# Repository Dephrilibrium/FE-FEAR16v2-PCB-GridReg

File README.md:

# FEAR-Grid Regulation
This repository contains the KiCAD-design files for a shield of the F(ield) E(mission) A(rray) R(egulation) current control circuit.

**Note:** This project is part of the SubModule-repository [FE-FEAR16v2][FE-FEAR16v2-SubmoduleRepo], where you can find sub-repositories for other shield-PCBs, mainboard-PCB and the firmware.

# Description
The name "grid regulation" comes from the original main purpose of regulating the potential of the extraction grid (extraction voltage) of a field emission array (FEA = cathode) based on the current through the cathode. However, it can be used in all cases where a potential needs to be regulation (Grid-input) based on the current-flow through the device under test which can be connected on a separate measurement-input (FEA-input). During active regulation this shield acts like a current-source/-sink.

- The shield itself takes 1 DAC-output voltage (V~Ctrl~ = 0..10V) to adjust the current control.
- The A(mperemeter) is actually a shunt-resistor which defines the measurable current range. A 1MΩ for instance yields a range from 0.31 nA (resolution) to 10 µA, whereby its wisely to keep the current slightly below as 10 µA is the absolute maximum measurable value.
- The V(oltmeter) measures the internal voltage-drop over the FET.

**Note:** Both, A and V use potentiometers to adjust their feedback-loop amplification. Due to tolerances on all the parts, its recommended to use a shield only at a specific mainboard and a specific channel-position at which the boards were calibrated.

**Principle of the cathode regulation:**

# HowTo to connect (samples and for calibration)
1. Place a shield on a mainboard/channel-slot.

2. Calibration: continue with step 3., otherwise go to 5.

3. Calibrate V~Shnt~ (FEA-Input)

    1. Connect the positive supply of a voltage source (needs to supply voltages up to 10V) to the FEA-input via an amperemeter (see figure above) and the negative supply (GND) to the HV- input. Note that amperemeter for fine-tuning the V~Shnt~ measurement (FEA-Input) is located between FEA-Input and FEA for circuitry reasons. As over the GridReg-Shield a voltage-drop occurs (up to 10V), the amperemeter needs to be able to withstand a few volts between measurement input and earth.

    2. Apply a voltage to the input (e.g. 9V).

    3. Adjust the current gain potentiometer, so that the measured ADC value divided by the shunt-resistance is equal to the amperemeter-value (V~Shnt~/R~Shunt~ = I~Amperemeter~)

4. Calibrate V~Drp~ (Grid-Input)

    1. Make sure, the FEA-Input connection of 3.i. above was made.

    2. Connect a high voltage-supply (via a Load-Resistor R~L~) to the Grid-Supply-Input (for further explanations see note below) and apply a high voltage (e.g. 1kV).

    3. Adjust the FEA-input voltage of 3.ii., so that the NFET blocks the current flow (Grid-Potential should increase to 1kV). If the FEA-Input voltage has to be higher or lower than V~Ctrl~ depends if you use the additional inverter-option which can be connected to the NFET-gate on the PCB.

    4. Adjust the voltage-drop gain potentiometer. The board projects a voltage range of &pm;1500V into a range of &pm;10V using a voltage divider with huge resistance values. Example for positive voltage:
    1500V * 5GΩ / 1005GΩ * Gain = 7.462..V * Gain = 10V
    Gain = 10V / 7.462..V = 1.34

5. Connect your FEA on the shield's FEA-Input screw terminal, the extraction grid to the the most negative supply to to HV- (which is the mainboard's common-terminal).

**Note:**
- The load-resistor R~L~ is a simple approach of increasing the voltage on the Grid-Input. This is because the high voltage of up to 1500V makes a  performant half-bridge design (regulated PFET instead of R~L~) tricky to realize. Its also noteworthy that R~L~ creates an asymmetric time-behaviour in charging and discharging the voltage of the extraction grid, and depends on the speeds your applications require.
- The FEAR command-documentation can be found in the firmware-repository (see [FE-FEAR16v2 Submodule-Repo][FE-FEAR16v2-SubmoduleRepo]).

[FE-FEAR16v2-SubmoduleRepo]: https://github.com/Dephrilibrium/FE-FEAR16v2

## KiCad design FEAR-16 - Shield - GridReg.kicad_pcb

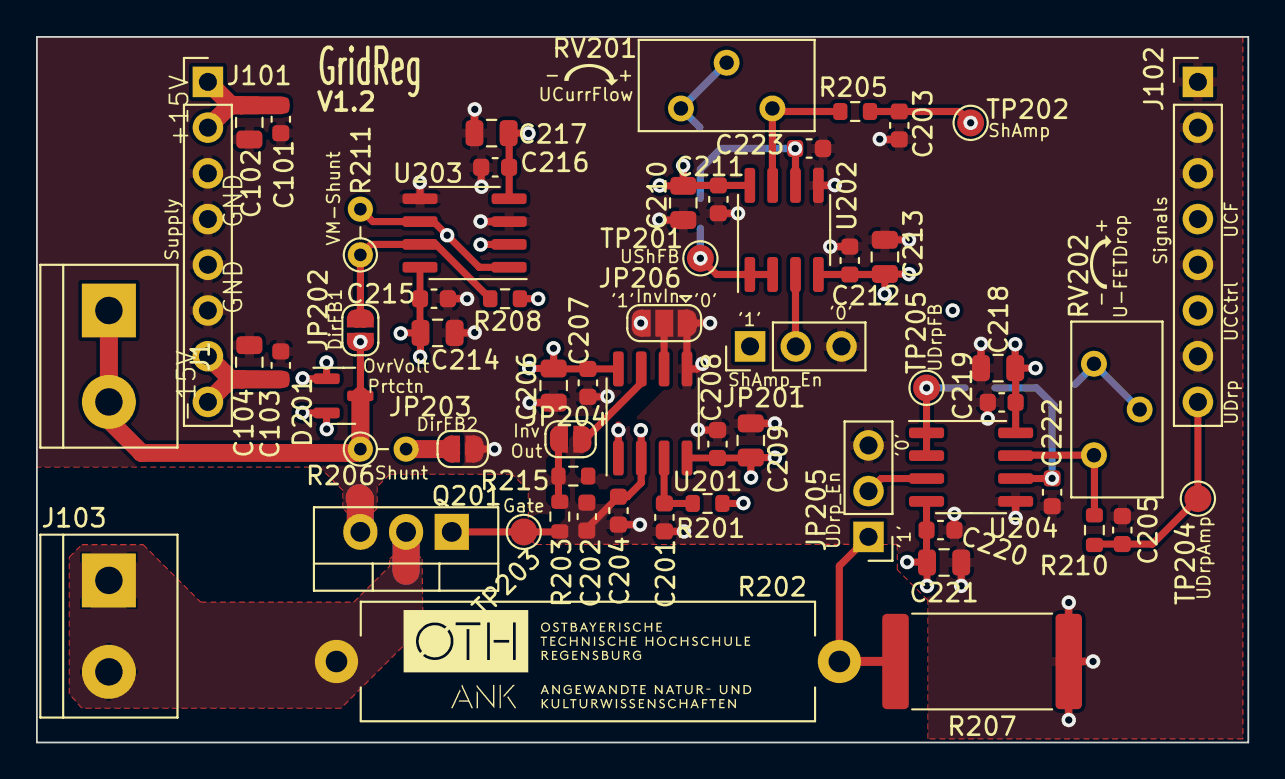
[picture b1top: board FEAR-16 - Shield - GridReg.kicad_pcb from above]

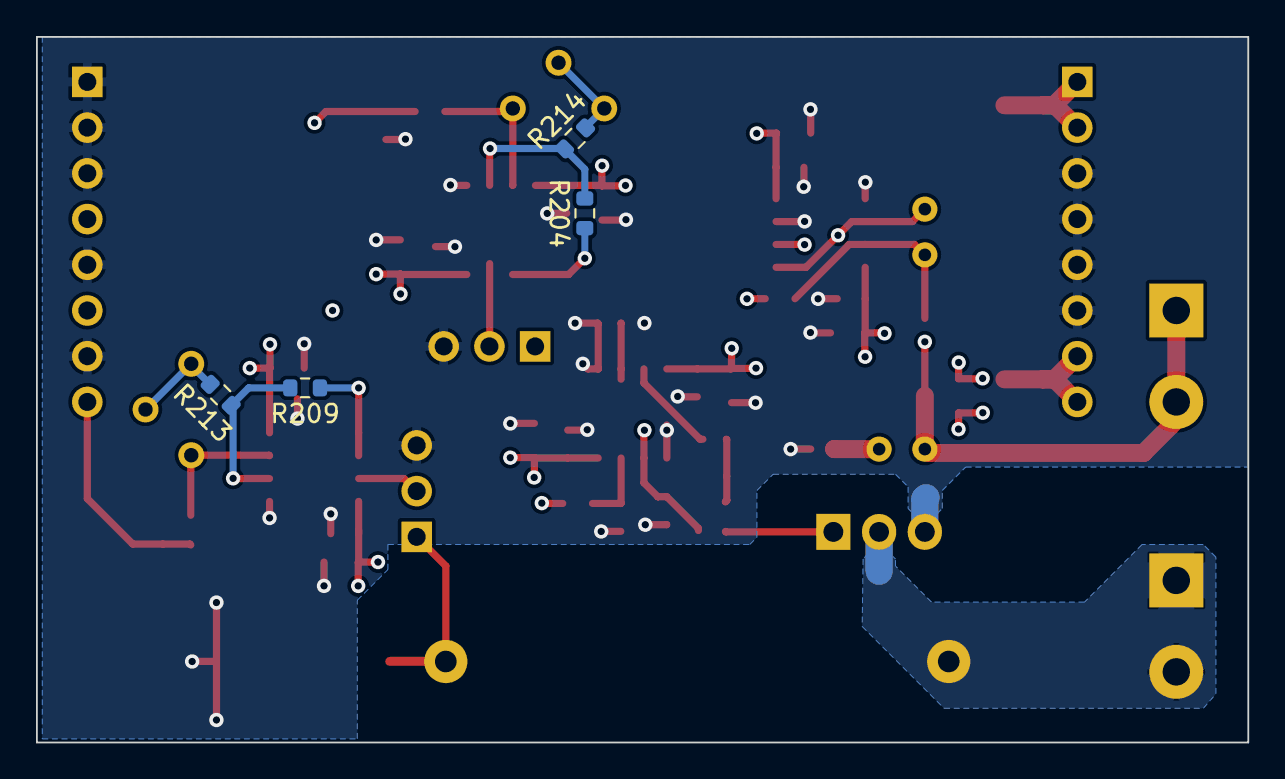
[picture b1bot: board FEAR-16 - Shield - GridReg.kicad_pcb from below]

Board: 4 copper layers, 67.3 x 39.2 mm, 64 parts (4 on the bottom side), 28 nets.

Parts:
C101, C103, C202, C207, C208, C211, C212, C215, C216, C219, C220: 100n/25V; C_0603_1608Metric
C102, C104, C206, C209, C210, C213, C214, C217, C218, C221: 10µ/25V; C_0805_2012Metric
C201: 1n/25V; C_0603_1608Metric
C203, C205: 470p/25V; C_0603_1608Metric
C204: 1n/25V (opt.); C_0603_1608Metric
C222, C223: 220n/25V; C_0603_1608Metric
D201: BAV99; SOT-23
J1, J103: Channel-In; TerminalBlock_bornier-2_P5.08mm
J101: Supply; PinHeader_1x08_P2.54mm_Vertical
J102: Signals; PinHeader_1x08_P2.54mm_Vertical
JP201: ShAmp_En; PinHeader_1x03_P2.54mm_Vertical
JP202: DirFB1; SolderJumper-2_P1.3mm_Open_RoundedPad1.0x1.5mm
JP203: DirFB2; SolderJumper-2_P1.3mm_Open_RoundedPad1.0x1.5mm
JP204: Invert_{Out}; SolderJumper-2_P1.3mm_Open_RoundedPad1.0x1.5mm
JP205: UDrp_En; PinHeader_1x03_P2.54mm_Vertical
JP206: Invert_{In}; SolderJumper-3_P1.3mm_Open_RoundedPad1.0x1.5mm
Q201: NDFPD1N150CG; TO-220-3_Vertical
R201: 1k; R_0603_1608Metric
R202: 1T/5%; R_Axial_Power_L25.0mm_W6.4mm_P27.94mm
R203: 220R; R_0603_1608Metric
R204, R205, R209, R210, R213, R214: 100k; R_0603_1608Metric
R206: Shunt; R_Axial_DIN0204_L3.6mm_D1.6mm_P2.54mm_Vertical
R207: 5G/5%; R_4020_10251Metric
R208: 220R (opt); R_0603_1608Metric
R211: VM-Shunt; R_Axial_DIN0204_L3.6mm_D1.6mm_P2.54mm_Vertical
R215: 1Meg; R_0603_1608Metric
RV201, RV202: 50k; Potentiometer_Bourns_3296Y_Vertical
TP201: UShFB; TestPoint_Pad_D1.5mm
TP202: ShAmp; TestPoint_Pad_D1.5mm
TP203: Gate; TestPoint_Pad_D1.5mm
TP204: UDrpAmp; TestPoint_Pad_D1.5mm
TP205: UDrpFB; TestPoint_Pad_D1.5mm
U201, U202, U203, U204: OPA2156xD; SOIC-8_3.9x4.9mm_P1.27mm

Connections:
+15V: C101.2, C102.2, C206.2, C207.2, C210.2, C211.2, C214.2, C215.2, C218.2, C219.2, D201.2 (A), J101.1, J101.2, U201.8 (V+), U202.8 (V+), U203.8 (V+), U204.8 (V+)
-15V: C103.1, C104.1, C208.2, C209.2, C212.2, C213.2, C216.2, C217.2, C220.2, C221.2, D201.1 (K), J101.7, J101.8, U201.4 (V-), U202.4 (V-), U203.4 (V-), U204.4 (V-)
/CathIn: D201.3 (K), J1.1, J1.2, JP202.2 (B), R206.1, U203.2 (-)
/Channel/UDrp: JP205.1 (A), R202.1, R207.2
/Channel/USh: C202.1, C204.2, JP201.1 (A), R208.2, U201.2 (-)
/GridIn: J103.1, J103.2, Q201.2 (D), R202.2
/UCurrCtrl: J102.6, R201.1
/UCurrFlow: C203.2, J102.4, R205.1, TP202.1
/UFETDrop: C205.2, J102.8, R210.1, TP204.1
GND: C101.1, C102.1, C103.2, C104.2, C201.2, C203.1, C204.1, C205.1, C206.1, C207.1, C208.1, C209.1, C210.1, C211.1, C212.1, C213.1, C214.1, C215.1, C216.1, C217.1, C218.1, C219.1, C220.1, C221.1, C222.1, C223.1, J101.3, J101.4, J101.5, J101.6, J102.1, J102.2, J102.3, J102.5, J102.7, JP201.3 (B), JP203.2 (B), JP205.3 (B), JP206.1 (A), Q201.3 (S), R207.1, U201.5 (+), U202.5 (+), U203.3 (+), U203.5 (+), U204.5 (+)
unnamed: JP201.2 (C), U202.3 (+)
unnamed: JP202.1 (A), R208.1, R211.1, U203.7
unnamed: JP203.1 (A), R206.2, R211.2, U203.1, U203.6 (-)
unnamed: JP204.1 (A), R203.1, R215.2
unnamed: JP204.2 (B), U201.7
unnamed: JP205.2 (C), U204.3 (+)
unnamed: C202.2, JP206.3 (B), R215.1, U201.1
unnamed: JP206.2 (C), U201.6 (-)
unnamed: Q201.1 (G), R203.2, TP203.1
unnamed: R205.2, RV201.3, U202.7
unnamed: R210.2, RV202.3, U204.7
unnamed: R213.2, RV202.1, RV202.2
unnamed: R214.2, RV201.1, RV201.2
unnamed: C201.1, R201.2, U201.3 (+)
unnamed: R204.1, TP201.1, U202.1, U202.2 (-)
unnamed: C223.2, R204.2, R214.1, U202.6 (-)
unnamed: R209.1, TP205.1, U204.1, U204.2 (-)
unnamed: C222.2, R209.2, R213.1, U204.6 (-)

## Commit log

2024-09-04 Added option to invert FET-Gate voltage
    Added JP206 (3Pad Solder Jumper) and JP204 (2Pad Solder Jumper)
    These using the, until now, unused second OpAmp of U201.
    --> Jumpers that allow to invert the FET-Gate Voltage
    FET-Gate Voltage acts as Grid-Regulation (inverting):
    - Close JP206 Pins 2 with 3
    - Close JP204
2024-09-04 Added kicad .lck files to gitignore
2024-09-12 Added comments on UFET feedback loop
2024-09-13 Finished initial README.md
